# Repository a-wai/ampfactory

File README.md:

Amp Factory
===========

Amp Factory is a collection of free (as in "free speech", not "free beer") electronic schematics for tube amplifiers dedicated to guitar and bass.

A-wai Amplification
-------------------

The documents in the "a-wai" directory are the schematics for amplifiers manufactured by A-wai Amplification, a one-person company building handwired amplifiers in Toulouse, France.

These schematics are licensed under the terms of the version 3 of the GNU General Public License. Therefore, you are granted the right to use, modify and/or redistribute these documents under certain conditions, listed in the GNU General Public License (see LICENSE file or the GNU website at http://www.gnu.org/licenses/).

The schematics are offered in two file formats :
- a .pdf for easy viewing and printing
- a .jsch file, which you can edit using the JSchem free software (http://dhost.info/jschem/)

Contributed schematics
----------------------

The "contrib" directory holds the schematics for amplifiers not manufactured by A-wai Amplification.

These schematics are the property of their respective owners, while still being offered under the terms of a free software license.

In that respect, they are also provided in a printable pdf version, as well as an editable version.

Non-free schematics
-------------------

Finally, the "non-free" directory holds a collection of schematics gathered from the web. These schematics are only available in printable form, and you cannot modify these files.

How to contribute
=================

You can send me your schematics to :
	info [AT] a-wai [DOTCOM]

Please be aware that any contribution has to relate to an amplifier already built and proven to work as expected, and be offered under a GPL-compatible license, in both printable and editable file formats.

There may be a few exceptions regarding very rare amplifiers which would present a particular interest from a technical point of view, but they must be strictly considered this way -- exceptions.

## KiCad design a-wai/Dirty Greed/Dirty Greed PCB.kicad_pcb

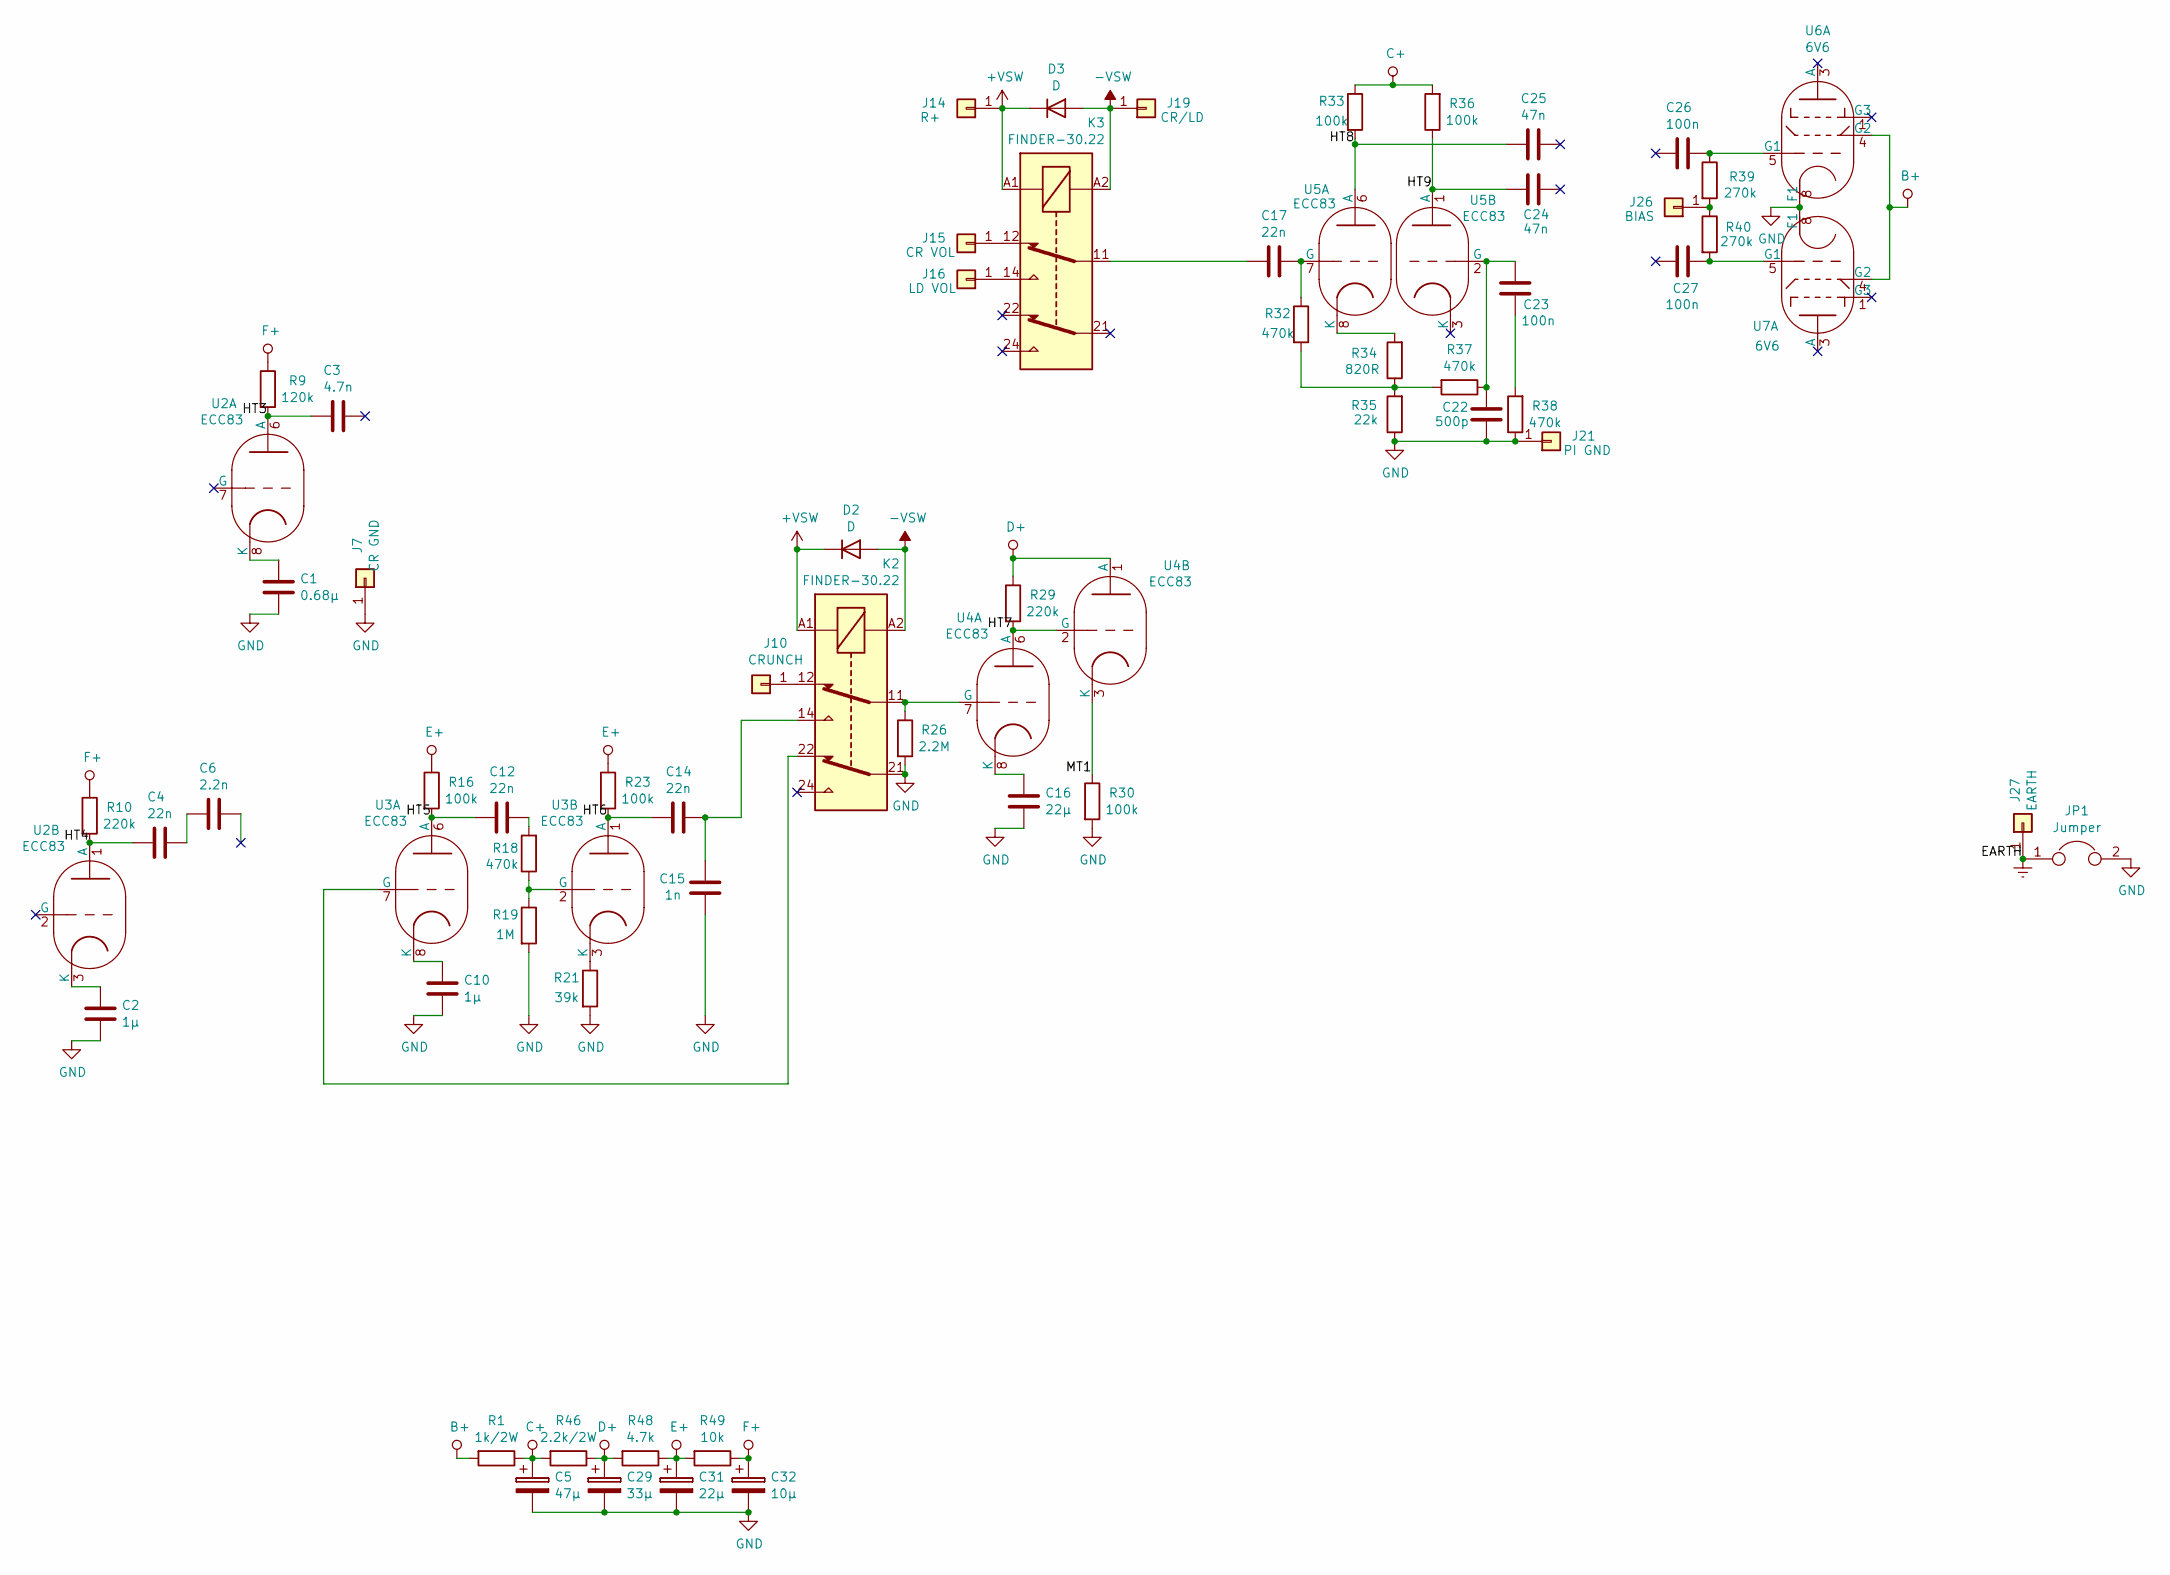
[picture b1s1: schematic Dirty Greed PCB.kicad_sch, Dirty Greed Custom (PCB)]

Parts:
C1: 0.68µ; C_M150_684_100V
C2, C10: 1µ; C_M150_105_100V
C3: 4.7n; C_6PS_502
C4, C12, C14, C17: 22n; C_WMF_223_630V
C5: 47µ; CP_Radial_D22.0mm_P10.00mm_SnapIn
C6: 2.2n; C_6PS_202
C15: 1n; C_WMF_102_630V
C16: 22µ; C_M150_105_100V
C22: 500p; C_SM_500V
C23, C26, C27: 100n; C_M150_104_630V
C24, C25: 47n; C_6PS_503
C29: 33µ; CPA_22uF_500V
C31: 22µ; CPA_22uF_500V
C32: 10µ; CPA_22uF_500V
D2, D3: D; D_DO-41_SOD81_P7.62mm_Horizontal
J7: CR GND; TURRET
J10: CRUNCH; TURRET
J14: R+; TURRET
J15: CR VOL; TURRET
J16: LD VOL; TURRET
J19: CR/LD; TURRET
J21: PI GND; TURRET
J26: BIAS; TURRET
J27: EARTH; TURRET
JP1: Jumper; SolderJumper-2_P1.3mm_Bridged_Pad1.0x1.5mm
K2, K3: FINDER-30.22; Relay_DPDT_Finder_30.22
R1: 1k/2W; R_2W
R9: 120k; R_0.5W
R10, R29: 220k; R_0.5W
R16, R23, R30, R33, R36: 100k; R_0.5W
R18, R32, R37, R38: 470k; R_0.5W
R19: 1M; R_0.5W
R21: 39k; R_0.5W
R26: 2.2M; R_0.5W
R34: 820R; R_0.5W
R35: 22k; R_0.5W
R39, R40: 270k; R_0.5W
R46: 2.2k/2W; R_2W
R48: 4.7k; R_0.5W
R49: 10k; R_0.5W
U2, U3, U4, U5: ECC83; TUBE_TRIODE
U6, U7: 6V6; TUBE_PENTODE

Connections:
+VSW: D2.1 (K), D3.1 (K), J14.1, K2.A1, K3.A1
-VSW: D2.2 (A), D3.2 (A), J19.1, K2.A2, K3.A2
/HT3: C3.2, R9.2, U2.6 (A)
/HT4: C4.2, R10.2, U2.1 (A)
/HT5: C12.2, R16.2, U3.6 (A)
/HT6: C14.2, R23.2, U3.1 (A)
/HT7: R29.2, U4.2 (G), U4.6 (A)
/HT8: C25.2, R33.2, U5.6 (A)
/HT9: C24.2, R36.1, U5.1 (A)
/MT1: R30.1, U4.3 (K)
B+: R1.2, U6.4 (G2), U7.4 (G2)
C+: C5.1, R1.1, R33.1, R36.2, R46.2
D+: C29.1, R29.1, R46.1, R48.2, U4.1 (A)
E+: C31.1, R16.1, R23.1, R48.1, R49.2
Earth: J27.1, JP1.1
F+: C32.1, R9.1, R10.1, R49.1
GND: C1.2, C2.2, C5.2, C10.2, C15.2, C16.2, C22.2, C29.2, C31.2, C32.2, J7.1, J21.1, JP1.2, K2.21, R19.2, R21.2, R26.2, R30.2, R35.1, R38.1, U6.8 (F1), U7.8 (F1)
unnamed: C4.1, C6.2
unnamed: C12.1, R18.2
unnamed: C14.1, C15.1, K2.14
unnamed: C17.2, K3.11
unnamed: C23.2, R38.2
unnamed: J10.1, K2.12
unnamed: J15.1, K3.12
unnamed: J16.1, K3.14
unnamed: J26.1, R39.2, R40.1
unnamed: R32.2, R34.1, R35.2, R37.2
unnamed: C1.1, U2.8 (K)
unnamed: C2.1, U2.3 (K)
unnamed: K2.22, U3.7 (G)
unnamed: C10.1, U3.8 (K)
unnamed: R18.1, R19.1, U3.2 (G)
unnamed: R21.1, U3.3 (K)
unnamed: K2.11, R26.1, U4.7 (G)
unnamed: C16.1, U4.8 (K)
unnamed: C17.1, R32.1, U5.7 (G)
unnamed: R34.2, U5.8 (K)
unnamed: C22.1, C23.1, R37.1, U5.2 (G)
unnamed: C26.1, R39.1, U6.5 (G1)
unnamed: C27.1, R40.2, U7.5 (G1)

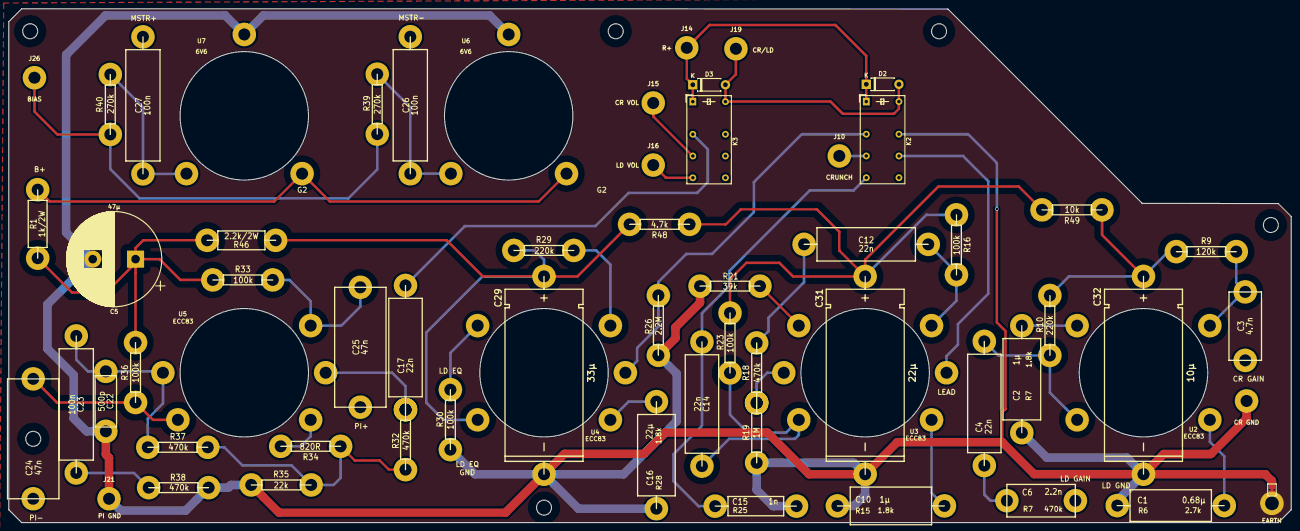
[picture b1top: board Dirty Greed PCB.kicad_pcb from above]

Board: 2 copper layers, 299.5 x 120.0 mm, 64 parts (0 on the bottom side), 40 nets.

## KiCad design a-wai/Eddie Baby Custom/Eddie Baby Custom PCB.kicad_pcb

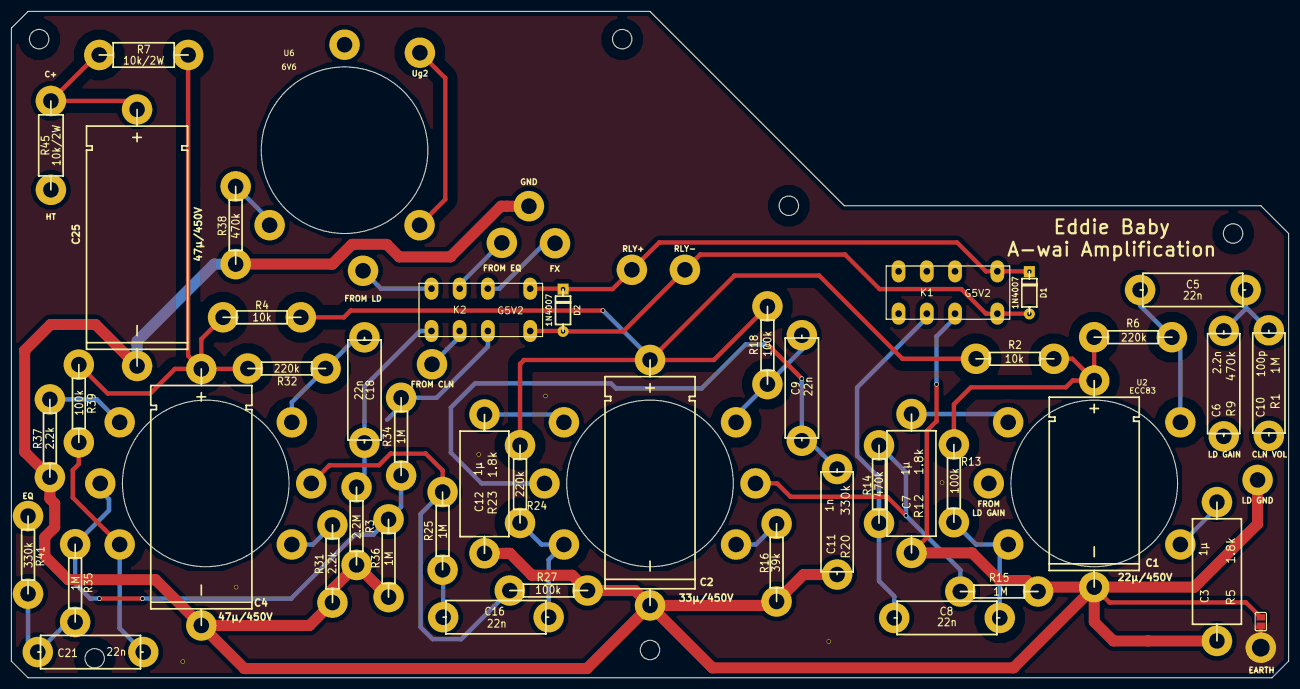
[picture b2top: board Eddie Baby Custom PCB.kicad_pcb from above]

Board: 2 copper layers, 230.0 x 120.0 mm, 65 parts (1 on the bottom side), 36 nets.

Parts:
C1: 22µ/450V; CPA_22uF_450V
C2: 33µ/450V; CPA_33uF_450V
C3, C7, C12: 1µ; C_M150_105_100V
C4, C25: 47µ/450V; CPA_47uF_450V
C5, C8, C9, C16, C18, C21: 22n; C_225P_223_400V
C6: 2.2n; C_225P_472_400V
C10: 100p; C_225P_472_400V
C11: 1n; C_225P_472_400V
D1, D2: 1N4007; DIODE
JP1: JUMPER; SJ_OPEN
JP2: JUMPER; SMB_Handsoldering
K1, K2: G5V2; relay-G5V2
P1: RLY+; TURRET
P2: RLY-; TURRET
P6: GND; TURRET
P9: FROM CLN; TURRET
P10: FROM EQ; TURRET
P11: Ug2; TURRET
P12: FROM LD; TURRET
P13: FX; TURRET
P14: EARTH; TURRET
P15: LD GND; TURRET
R2, R4: 10k; R_0.5W
R3: 2.2M; R_0.5W
R6, R24, R32: 220k; R_0.5W
R7, R45: 10k/2W; R_2W
R13, R18, R27, R39: 100k; R_0.5W
R14, R38: 470k; R_0.5W
R15, R25, R34, R35, R36: 1M; R_0.5W
R16: 39k; R_0.5W
R31, R37: 2.2k; R_0.5W
R41: 330k; R_0.5W
TURRET: P***; TURRET
TURRET#2, TURRET#3, TURRET#4, TURRET#5, TURRET#6: P***; TURRET
U2, U3, U4: ECC83; TUBE_TRIODE
U6: 6V6; TUBE_PENTODE

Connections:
/HT_G2: P11.1, U6.9
/HT_U2A: C5.1, R6.2, U2.6
/HT_U2B: C8.1, R13.2, U2.1
/HT_U3A: C9.1, R18.2, U3.6
/HT_U3B: C16.1, R24.2, U3.1
/HT_U4A: C18.1, R32.2, U4.6
/HT_U4B: C21.1, R39.2, U4.1
C+: C25.1, R7.1, R45.2
D+: C4.1, R4.1, R7.2, R32.1, R39.1
E+: C2.1, R2.1, R4.2, R18.1, R24.1
Earth: JP1.2, P14.1, TURRET.1, TURRET#2.1, TURRET#3.1, TURRET#4.1, TURRET#5.1, TURRET#6.1
F+: C1.1, R2.2, R6.1, R13.1
GND: C1.2, C2.2, C3.2, C4.2, C7.2, C11.2, C12.2, C25.2, JP1.1, K1.13, P6.1, P15.1, R3.2, R15.2, R16.2, R27.2, R31.2, R36.2, R37.2, R38.2
unnamed: C3.1, U2.8
unnamed: C7.1, U2.3
unnamed: C8.2, K1.11, R14.1
unnamed: C5.2, C6.1, C10.2
unnamed: C9.2, C11.1, U3.2
unnamed: C12.1, U3.3
unnamed: C16.2, R25.1
unnamed: C18.2, JP2.1, K2.9, R3.1
unnamed: C21.2, R35.1, R41.2
unnamed: D1.1, D2.1, K1.1, K2.1, P1.1
unnamed: D1.2, D2.2, K1.16, K2.16, P2.1
unnamed: JP2.2, K2.13, R34.2
unnamed: K2.4, P13.1
unnamed: K2.6, P10.1
unnamed: K2.8, P12.1
unnamed: K2.11, P9.1
unnamed: R38.1, U6.2
unnamed: R14.2, R15.1, U3.7
unnamed: R16.1, U3.8
unnamed: R25.2, R27.1, U4.7
unnamed: R31.1, U4.8
unnamed: R34.1, R35.2, R36.1, U4.2
unnamed: R37.1, U4.3

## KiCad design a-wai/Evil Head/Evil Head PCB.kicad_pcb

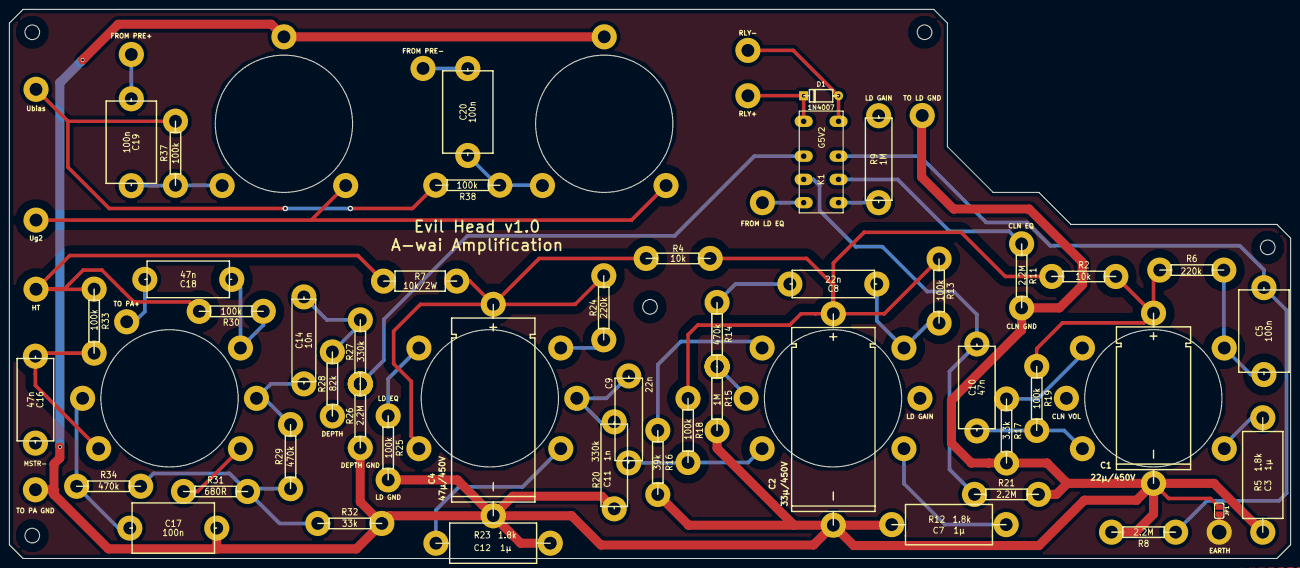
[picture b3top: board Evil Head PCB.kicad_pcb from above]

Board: 2 copper layers, 280.0 x 120.0 mm, 71 parts (0 on the bottom side), 42 nets.

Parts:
C1: 22µ/450V; CPA_22uF_450V
C2: 33µ/450V; CPA_33uF_500V
C4: 47µ/450V; CPA_47uF_450V
C5, C17, C19, C20: 100n; C_225P_104_400V
C8, C9: 22n; C_225P_223_400V
C10, C16, C18: 47n; C_225P_473_400V
C14: 10n; C_225P_103_400V
D1: 1N4007; DIODE
JP1: JUMPER; SJ_OPEN
K1: G5V2; relay-G5V2
P1: RLY+; TURRET
P2: RLY-; TURRET
P3: HT; TURRET
P6: FROM LD EQ; TURRET
P9: TO PA+; TURRET
P10: FROM PRE+; TURRET
P11: Ug2; TURRET
P12: Ubias; TURRET
P13: FROM PRE-; TURRET
P14: EARTH; TURRET
P15: TO LD GND; TURRET
P20: TO PA GND; TURRET
R2, R4: 10k; R_0.5W
R5, R12, R23: 1.8k; C_M150_105_100V
R6, R24: 220k; R_0.5W
R7: 10k/2W; R_2W
R8, R11, R21, R26: 2.2M; R_0.5W
R9: 1M; C_225P_472_400V
R13, R18, R19, R25, R30, R33, R37, R38: 100k; R_0.5W
R14, R29, R34: 470k; R_0.5W
R15: 1M; R_0.5W
R16: 39k; R_0.5W
R17: 3.3k; R_0.5W
R20: 330k; C_225P_472_400V
R27: 330k; R_0.5W
R28: 82k; R_0.5W
R31: 680R; R_0.5W
R32: 33k; R_0.5W
REF: ø3.2; MountingHole_3mm
REF#2, REF#3, REF#4, REF#5: ø3.2; MountingHole_3mm
U1, U2, U3, U4: ECC83; TUBE_TRIODE
U5, U6: 6V6; TUBE_PENTODE

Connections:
/HT_G2: P11.1, U5.9, U6.9
/HT_U1A: C5.1, R6.2, U1.6
/HT_U1B: C10.1, R19.2, U1.1
/HT_U2A: C8.1, R13.2, U2.6
/HT_U2B: C9.1, R18.2, U2.1
/HT_U3A: R24.2, U3.6
/HT_U3B: R25.1, U3.3
/HT_U4A: C18.1, R30.2, U4.6
/HT_U4B: C16.1, R33.2, U4.1
C+: P3.1, R7.1, R30.1, R33.1
D+: C4.1, R4.1, R7.2, R24.1, U3.1
E+: C2.1, R2.1, R4.2, R13.1, R18.1
Earth: JP1.2, P14.1
F+: C1.1, R2.2, R6.1, R19.1
GND: C1.2, C2.2, C4.2, C17.2, JP1.1, P15.1, P20.1, R5.2, R8.2, R11.2, R12.2, R15.2, R16.2, R17.2, R20.2, R21.2, R23.2, R25.2, R26.2, R32.2, U5.3, U6.3
unnamed: R5.1, U1.8
unnamed: C5.2, K1.13, R8.1
unnamed: K1.9, R9.1
unnamed: R12.1, U2.8
unnamed: C8.2, R14.1
unnamed: C10.2, K1.6, R21.1
unnamed: C9.2, R20.1, U3.7
unnamed: R23.1, U3.8
unnamed: C14.1, R27.1, R28.1
unnamed: C14.2, R29.2, U4.7
unnamed: C17.1, R34.1, U4.2
unnamed: C18.2, P9.1
unnamed: C19.1, P10.1
unnamed: C19.2, R37.1, U5.2
unnamed: C20.1, R38.1, U6.2
unnamed: C20.2, P13.1
unnamed: D1.1, K1.1, P1.1
unnamed: D1.2, K1.16, P2.1
unnamed: K1.4, R26.1, R27.2
unnamed: K1.8, P6.1
unnamed: K1.11, R11.1
unnamed: P12.1, R37.2, R38.2
unnamed: R14.2, R15.1, U2.2
unnamed: R16.1, U2.3
unnamed: R17.1, U1.3
unnamed: R29.1, R31.2, R32.1, R34.2
unnamed: R31.1, U4.8

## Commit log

2013-12-11 Moving to directories
2013-12-11 Added the Black Betty
2013-12-11 Added old Marshall & Fender in non-free
2013-12-11 Added .gitignore
2013-12-12 Legal cleanup
2013-12-12 Update names
2014-07-08 Added Schneider "Choral" amp
2014-07-08 Added schematics from : - Dumble - Mesa/Boogie - Orange - Peavey - Vox
2014-07-08 Added Ampeg schematics
2014-07-08 Added McPinpin Electronics DP1B Bass Distortion
2014-09-21 Added Diezel VH-4
2015-08-23 Corrected Eddie Baby schematics
2015-09-01 Corrected Evil Head schematics
2015-09-23 Added AX84, Bogner, Jet City & Madamp + more Fender & Marshall
2015-09-23 Added more AX84
2015-09-23 Reorganisation
2015-09-24 Add Bad Cat, Blackheart, Crate, Dr Z, Egnater, Engl, Hiwatt, Kitty Hawk, Laney, Matamp, Matchless, Park, Soldano, Sovtek, Supro, top Hat & VHT
2015-09-25 Added EVH 5150 III
2015-09-25 Added EVH 100W 5150 III
2015-10-02 Added Peavey JSX
2015-10-03 Added Fortin, Friedman & more Marshall 50th anniv.
2015-10-06 Added SVT-CL (Ampeg), Dynacord, Egmond & Faylon
2015-10-12 Added Marshall DSL15 & DSL40C
2015-11-30 Added Blackstar HT-1
2015-12-16 Corrected components numbering for 3-wai XL
2016-03-16 Added Rocker 30 (preamp only)
2016-04-21 Modified Bass 200
2016-09-27 Redesigned the Evil Head with Kicad
2016-12-02 Add Orange AD200B
    Using Bernard D'uur schematics for the AD200B MkIII
2017-04-01 add TH30 preamp
2017-10-25 Add Bogner Alchemist
2017-10-25 Update Evil Head & add Evil Eddie
2017-12-02 Update Evil Eddie Schematics & PCB
2017-12-02 Update Evil Eddie Gerber files
2017-12-12 Add Friedman PT20 & SB50 + nicely drawn Bogner XTC preamp
2017-12-12 Update Bogner XTC
2018-02-23 Add Mesa Express 5:25 & 5:50
2018-04-16 Add files via upload
    Addition of Carvin V3M schemes
2018-04-16 Create Carvin
2018-04-16 Create test
2018-04-26 Change files name
2018-04-26 Rename Carvin V3M files & keep only complete versions
2019-02-15 Add "Fat Bastard" bass preamp
2019-02-27 Add custom Eddie Baby (w/ clean channel & FX loop)
2019-02-27 Add EVH 5150-III LBX
2019-04-25 Update fat bastard
2019-05-17 Update Fat Bastard to latest version
2019-07-11 Add 'DG Custom'
2024-02-29 Add Laney TT50 schematics
    Courtesy of @ewidance, thanks!
    Fixes #3
2025-03-09 Add Peavey 6505 MH & Soldano Avenger
2025-03-09 Add Kicad version of the Dirty Greed
2025-03-09 Dirty Greed: cut PCB some more
2025-03-09 Dirty Greed: add solder masks to Gerber files
2025-04-12 non-free: add some more schematics
    This adds the following new schematics:
    * Engl Fireball 25 & 100
    * Mesa Mini Rectifier
    * Orange Jim Root & Dual Terror
    * Orange Thunderverb preamp
    * Orange OR15 & TH30 (original schematics)
2025-04-22 non-free: Orange: add Rocker 30 PA + PS
2025-04-22 non-free: EVH: add 5150III LBXII
2026-06-16 Adding Egnater amps
